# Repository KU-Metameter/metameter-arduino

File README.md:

Bluetooth Multimeter Senior Design Project  
Contains Arduino files

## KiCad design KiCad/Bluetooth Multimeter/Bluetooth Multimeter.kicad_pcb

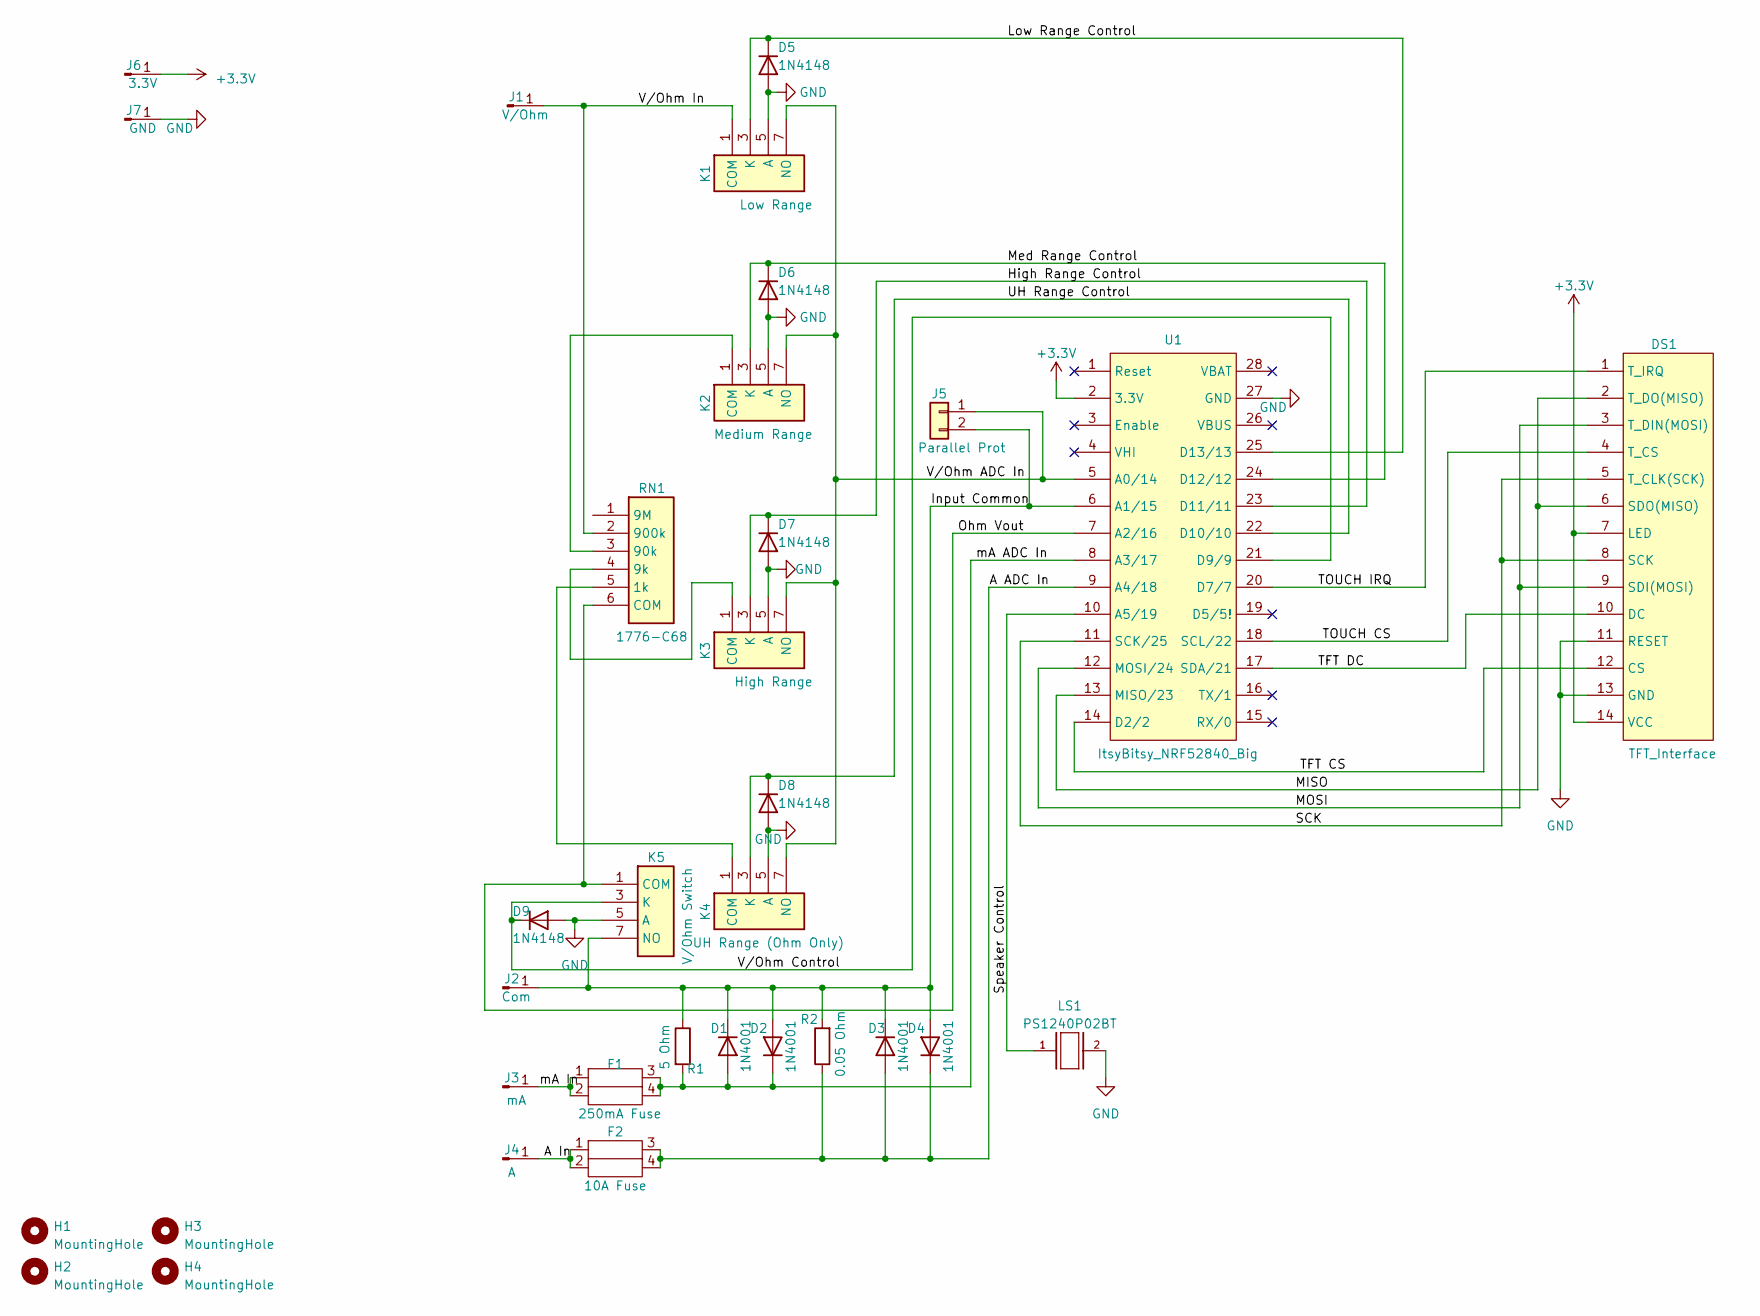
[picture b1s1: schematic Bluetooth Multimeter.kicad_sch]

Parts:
D1, D2, D3, D4: 1N4001; D_DO-41_SOD81_P10.16mm_Horizontal
D5, D6, D7, D8, D9: 1N4148; D_DO-35_SOD27_P7.62mm_Horizontal
DS1: TFT_Interface; PinHeader_1x14_P2.54mm_Vertical_H0.9mm
F1: 250mA Fuse; LF124061_1
F2: 10A Fuse; LF124041_4
H1, H2, H3, H4: MountingHole; MountingHole_3mm
J1: V/Ohm; PinHeader_1x01_P2.54mm_Vertical_H0.8mm
J2: Com; PinHeader_1x01_P2.54mm_Vertical_H0.8mm
J3: mA; PinHeader_1x01_P2.54mm_Vertical_H0.8mm
J4: A; PinHeader_1x01_P2.54mm_Vertical_H0.8mm
J5: Parallel Prot; PinHeader_1x02_P2.54mm_Vertical_H0.9mm
J6: 3.3V; PinHeader_1x01_P2.54mm_Vertical_H0.8mm
J7: GND; PinHeader_1x01_P2.54mm_Vertical_H0.8mm
K1: Low Range; SIL03-1A72-71_4; Manufacturer_Part_Number SIL03-1A72-71D; Mouser Part Number 876-SIL03-1A72-71D
K2: Medium Range; SIL03-1A72-71_4; Manufacturer_Part_Number SIL03-1A72-71D; Mouser Part Number 876-SIL03-1A72-71D
K3: High Range; SIL03-1A72-71_4; Manufacturer_Part_Number SIL03-1A72-71D; Mouser Part Number 876-SIL03-1A72-71D
K4: UH Range (Ohm Only); SIL03-1A72-71_4; Manufacturer_Part_Number SIL03-1A72-71D; Mouser Part Number 876-SIL03-1A72-71D
K5: V/Ohm Switch; SIL03-1A72-71_4; Manufacturer_Part_Number SIL03-1A72-71D; Mouser Part Number 876-SIL03-1A72-71D
LS1: PS1240P02BT; XDCR_PS1240P02BT
R1: 5 Ohm; R_Axial_DIN0207_L6.3mm_D2.5mm_P2.54mm_Vertical
R2: 0.05 Ohm; LOB-1528272_3
RN1: 1776-C68; 1776-C68-1; Manufacturer_Part_Number 1776-C68; Mouser Part Number 684-1776-C68
U1: ItsyBitsy_NRF52840_Big; ItsyBitsy

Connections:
+3.3V: DS1.7 (LED), DS1.14 (VCC), J6.1, U1.2 (3.3V)
/A ADC In: D3.2 (A), D4.1 (K), F2.3, F2.4, R2.1, U1.9 (A4/18)
/A In: F2.1, F2.2, J4.1
/High Range Control: D7.1 (K), K3.3 (K), U1.23 (D11/11)
/Input Common: D1.1 (K), D2.2 (A), D3.1 (K), D4.2 (A), J2.1, J5.2, K5.7 (NO), R1.1, R2.2, U1.6 (A1/15)
/Low Range Control: D5.1 (K), K1.3 (K), U1.25 (D13/13)
/MISO: DS1.2 (T_DO(MISO)), DS1.6 (SDO(MISO)), U1.13 (MISO/23)
/MOSI: DS1.3 (T_DIN(MOSI)), DS1.9 (SDI(MOSI)), U1.12 (MOSI/24)
/Med Range Control: D6.1 (K), K2.3 (K), U1.24 (D12/12)
/Ohm Vout: K5.1 (COM), RN1.6 (COM), U1.7 (A2/16)
/SCK: DS1.5 (T_CLK(SCK)), DS1.8 (SCK), U1.11 (SCK/25)
/Speaker Control: LS1.1, U1., U1.10 (A5/19)
/TFT CS: DS1.12 (CS), U1.14 (D2/2)
/TFT DC: DS1.10 (DC), U1.17 (SDA/21)
/TOUCH CS: DS1.4 (T_CS), U1.18 (SCL/22)
/TOUCH IRQ: DS1.1 (T_IRQ), U1.20 (D7/7)
/UH Range Control: D8.1 (K), K4.3 (K), U1.22 (D10/10)
/V/Ohm ADC In: J5.1, K1.7 (NO), K2.7 (NO), K3.7 (NO), K4.7 (NO), U1.5 (A0/14)
/V/Ohm Control: D9.1 (K), K5.3 (K), U1.21 (D9/9)
/V/Ohm In: J1.1, K1.1 (COM), RN1.2 (900k)
/mA ADC In: D1.2 (A), D2.1 (K), F1.3, F1.4, R1.2, U1.8 (A3/17)
/mA In: F1.1, F1.2, J3.1
GND: D5.2 (A), D6.2 (A), D7.2 (A), D8.2 (A), D9.2 (A), DS1.11 (RESET), DS1.13 (GND), J7.1, K1.5 (A), K2.5 (A), K3.5 (A), K4.5 (A), K5.5 (A), LS1.2, U1.27 (GND)
unnamed: K2.1 (COM), RN1.3 (90k)
unnamed: K3.1 (COM), RN1.4 (9k)
unnamed: K4.1 (COM), RN1.5 (1k)

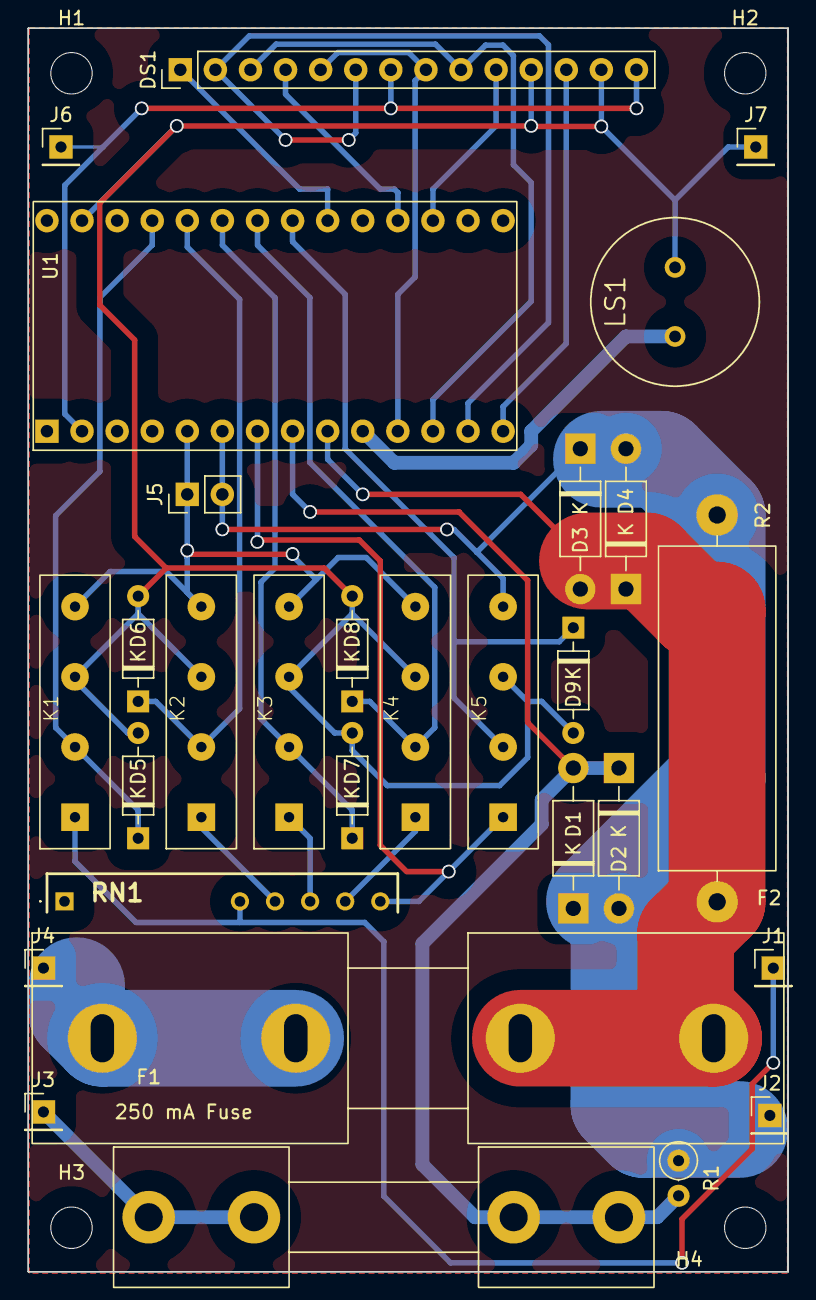
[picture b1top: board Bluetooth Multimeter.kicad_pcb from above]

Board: 2 copper layers, 55.0 x 90.0 mm, 33 parts (0 on the bottom side), 26 nets.

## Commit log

2023-03-09 joe mama
2023-03-10 Bluetooth Multimeter KiCad Project
2023-03-10 Modified README to be less stupid
2023-03-10 Moved BTMM KiCad Project into KiCad Directory
2023-03-10 Added Arduino Directory with test Display and Voltmeter projects
2023-03-11 I'm using git gui like an animal
2023-03-11 Added Symbols and Footprints, Rev 1 of Schematic and PCB
2023-03-11 Test Signed Commit
2023-03-12 Reformatted footprints & Routed PCB rev 2
2023-03-12 Slightly Modifided PCB
2023-03-16 began main arduino project, modified KiCad itsybitsy symbol
2023-03-17 prefinal compiles, needs physical testing
2023-03-17 added rev 4 of PCB, should be shoppable if footprints are correct
2023-03-18 finalized rev4, good to shop if footprints are correct
2023-03-21 finalized pcb rev 4 and sent to shop
2023-03-21 beep boop
2023-03-21 moved kicad files to seperate repository
2023-03-21 workingish multimeter sans bluetooth
2023-03-22 began work with piezo speaker
2023-03-26 fixed mA meter funciton
2023-03-26 added piezo functionality to main project
2023-03-28 add bluetooth
2023-04-04 modified main for 100k ladder, began diode meter
2023-04-06 Tested diode meter, working
2023-04-12 reverse UUIDs
2023-04-13 refactor bluetooth setup into one function
2023-04-13 Made print function better
2023-04-24 init bt support for other modes
2023-04-25 change notify to indicate
2023-04-27 tweak diode meter
2023-04-29 fixed voltmeter, added overrange to ohmeter
2023-05-01 use volts for initial mode
2023-05-01 use inf to represent out of range
2023-05-02 remotely change mode
2023-05-02 add continuity characteristic
